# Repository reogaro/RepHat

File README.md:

# RepHat

"**R**epRap **E**xtension for **P**i"-**Hat**

Designed in Kicad. Open Source Hardware.

> [!CAUTION]
> This project is still in development and not ready for use!

A Raspberry Pi Hat for controlling stepper motors. Intended to be a [RAMPS](https://reprap.org/wiki/RAMPS_1.4) for the Raspberry Pi.

Built for use with LinuxCNC. See [here](https://github.com/reogaro/linuxcnc-pi4b-gpio) for some configuration examples.

## Features:

- 12-24 V Input Voltage
- 5V for Raspberry Pi with TI LMR51450 Switching Regulator
- Four Toshiba TB67S109AFTG Stepper Drivers
- Four endstop inputs with selectable voltages
- Input protection

## Current progress

[Schematic](output/schematic.pdf): Complete
[Routing](output/routing.pdf): Work in progress

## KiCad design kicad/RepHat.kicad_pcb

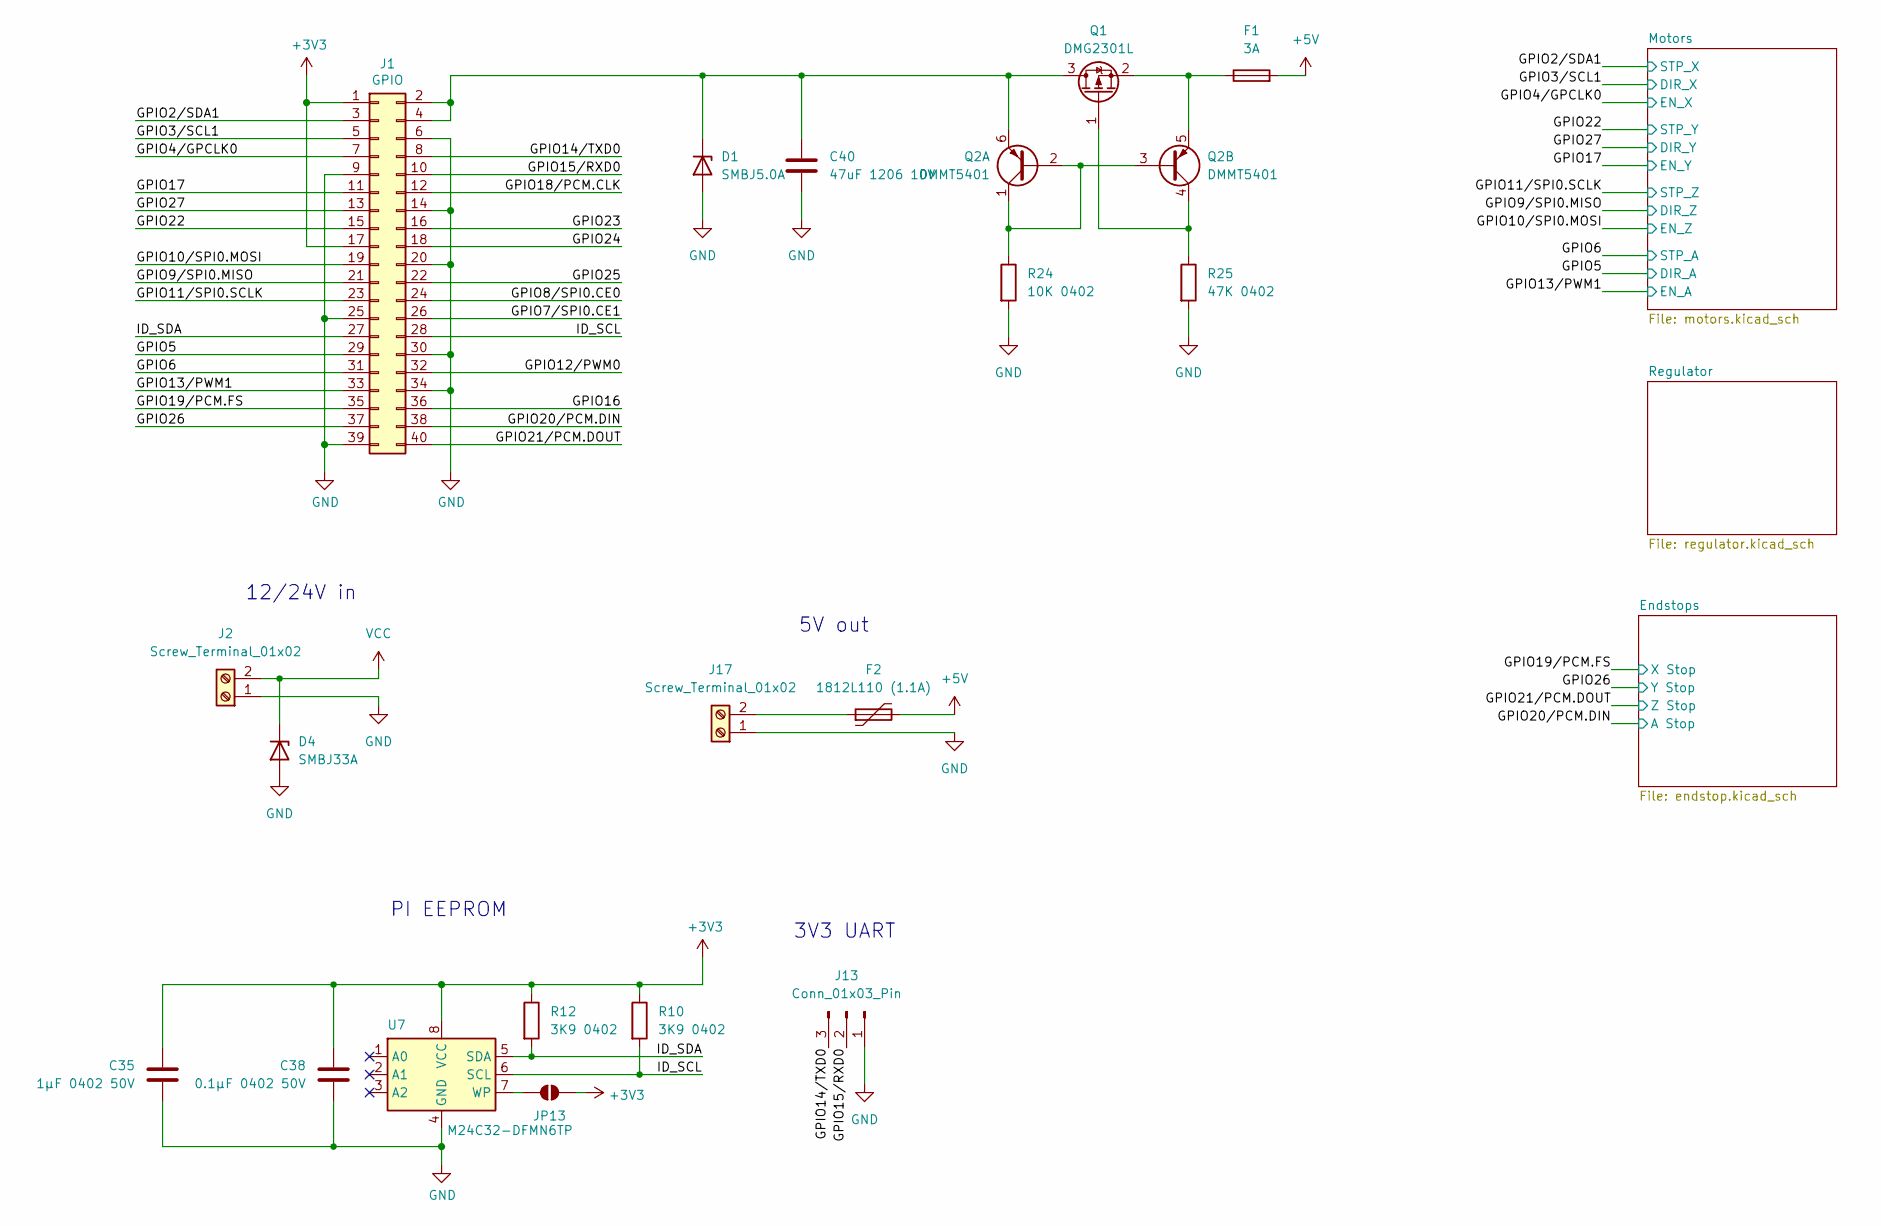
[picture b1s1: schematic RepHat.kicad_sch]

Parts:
C35: 1μF 0402 50V; C_0402_1005Metric
C38: 0.1μF 0402 50V; C_0402_1005Metric
C40: 47uF 1206 10V; C_1206_3216Metric
D1: SMBJ5.0A; D_SMB
D4: SMBJ33A; D_SMB
F1: 3A; Fuseholder_Littelfuse_Nano2_154x
F2: 1812L110 (1.1A); Fuse_1812_4532Metric
J1: GPIO; PinSocket_2x20_P2.54mm_Vertical
J2, J17: Screw_Terminal_01x02; TerminalBlock_bornier-2_P5.08mm
J13: Conn_01x03_Pin; PinHeader_1x03_P2.54mm_Vertical
JP13: ID_WP; SolderJumper-2_P1.3mm_Open_RoundedPad1.0x1.5mm
Q1: DMG2301L; SOT-23
Q2: DMMT5401; SOT-23-6
R10, R12: 3K9 0402; R_0402_1005Metric
R24: 10K 0402; R_0402_1005Metric
R25: 47K 0402; R_0402_1005Metric
U7: M24C32-DFMN6TP; SOIC-8_5.275x5.275mm_P1.27mm

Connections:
+3V3: C35.1, C38.1, J1.1, J1.17, JP13.2 (B), R10.1, R12.1, U7.8 (VCC); also elsewhere on the board
+5V: F1.2, F2.2; also elsewhere on the board
/GPIO2/SDA1: J1.3; also elsewhere on the board
/GPIO3/SCL1: J1.5; also elsewhere on the board
/GPIO4/GPCLK0: J1.7; also elsewhere on the board
/GPIO5: J1.29; also elsewhere on the board
/GPIO6: J1.31; also elsewhere on the board
/GPIO7/SPI0.CE1: J1.26
/GPIO8/SPI0.CE0: J1.24
/GPIO9/SPI0.MISO: J1.21; also elsewhere on the board
/GPIO10/SPI0.MOSI: J1.19; also elsewhere on the board
/GPIO11/SPI0.SCLK: J1.23; also elsewhere on the board
/GPIO12/PWM0: J1.32
/GPIO13/PWM1: J1.33; also elsewhere on the board
/GPIO14/TXD0: J1.8, J13.3
/GPIO15/RXD0: J1.10, J13.2
/GPIO16: J1.36
/GPIO17: J1.11; also elsewhere on the board
/GPIO18/PCM.CLK: J1.12
/GPIO19/PCM.FS: J1.35; also elsewhere on the board
/GPIO20/PCM.DIN: J1.38; also elsewhere on the board
/GPIO21/PCM.DOUT: J1.40; also elsewhere on the board
/GPIO22: J1.15; also elsewhere on the board
/GPIO23: J1.16
/GPIO24: J1.18
/GPIO25: J1.22
/GPIO26: J1.37; also elsewhere on the board
/GPIO27: J1.13; also elsewhere on the board
/ID_SCL: J1.28, R10.2, U7.6 (SCL)
/ID_SDA: J1.27, R12.2, U7.5 (SDA)
GND: C35.2, C38.2, C40.2, D1.2 (A), D4.2 (A), J1.6, J1.9, J1.14, J1.20, J1.25, J1.30, J1.34, J1.39, J2.1, J13.1, J17.1, R24.2, R25.2, U7.4 (GND); also elsewhere on the board
unnamed: C40.1, D1.1 (K), J1.2, J1.4, Q1.3 (D), Q2.6 (E1)
unnamed: F2.1, J17.2
unnamed: JP13.1 (A), U7.7 (WP)
unnamed: Q1.1 (G), Q2.4 (C2), R25.1
unnamed: F1.1, Q1.2 (S), Q2.5 (E2)
unnamed: Q2.1 (C1), Q2.2 (B1), Q2.3 (B2), R24.1
VCC: D4.1 (K), J2.2; also elsewhere on the board

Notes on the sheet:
12/24V in
PI EEPROM
5V out
3V3 UART

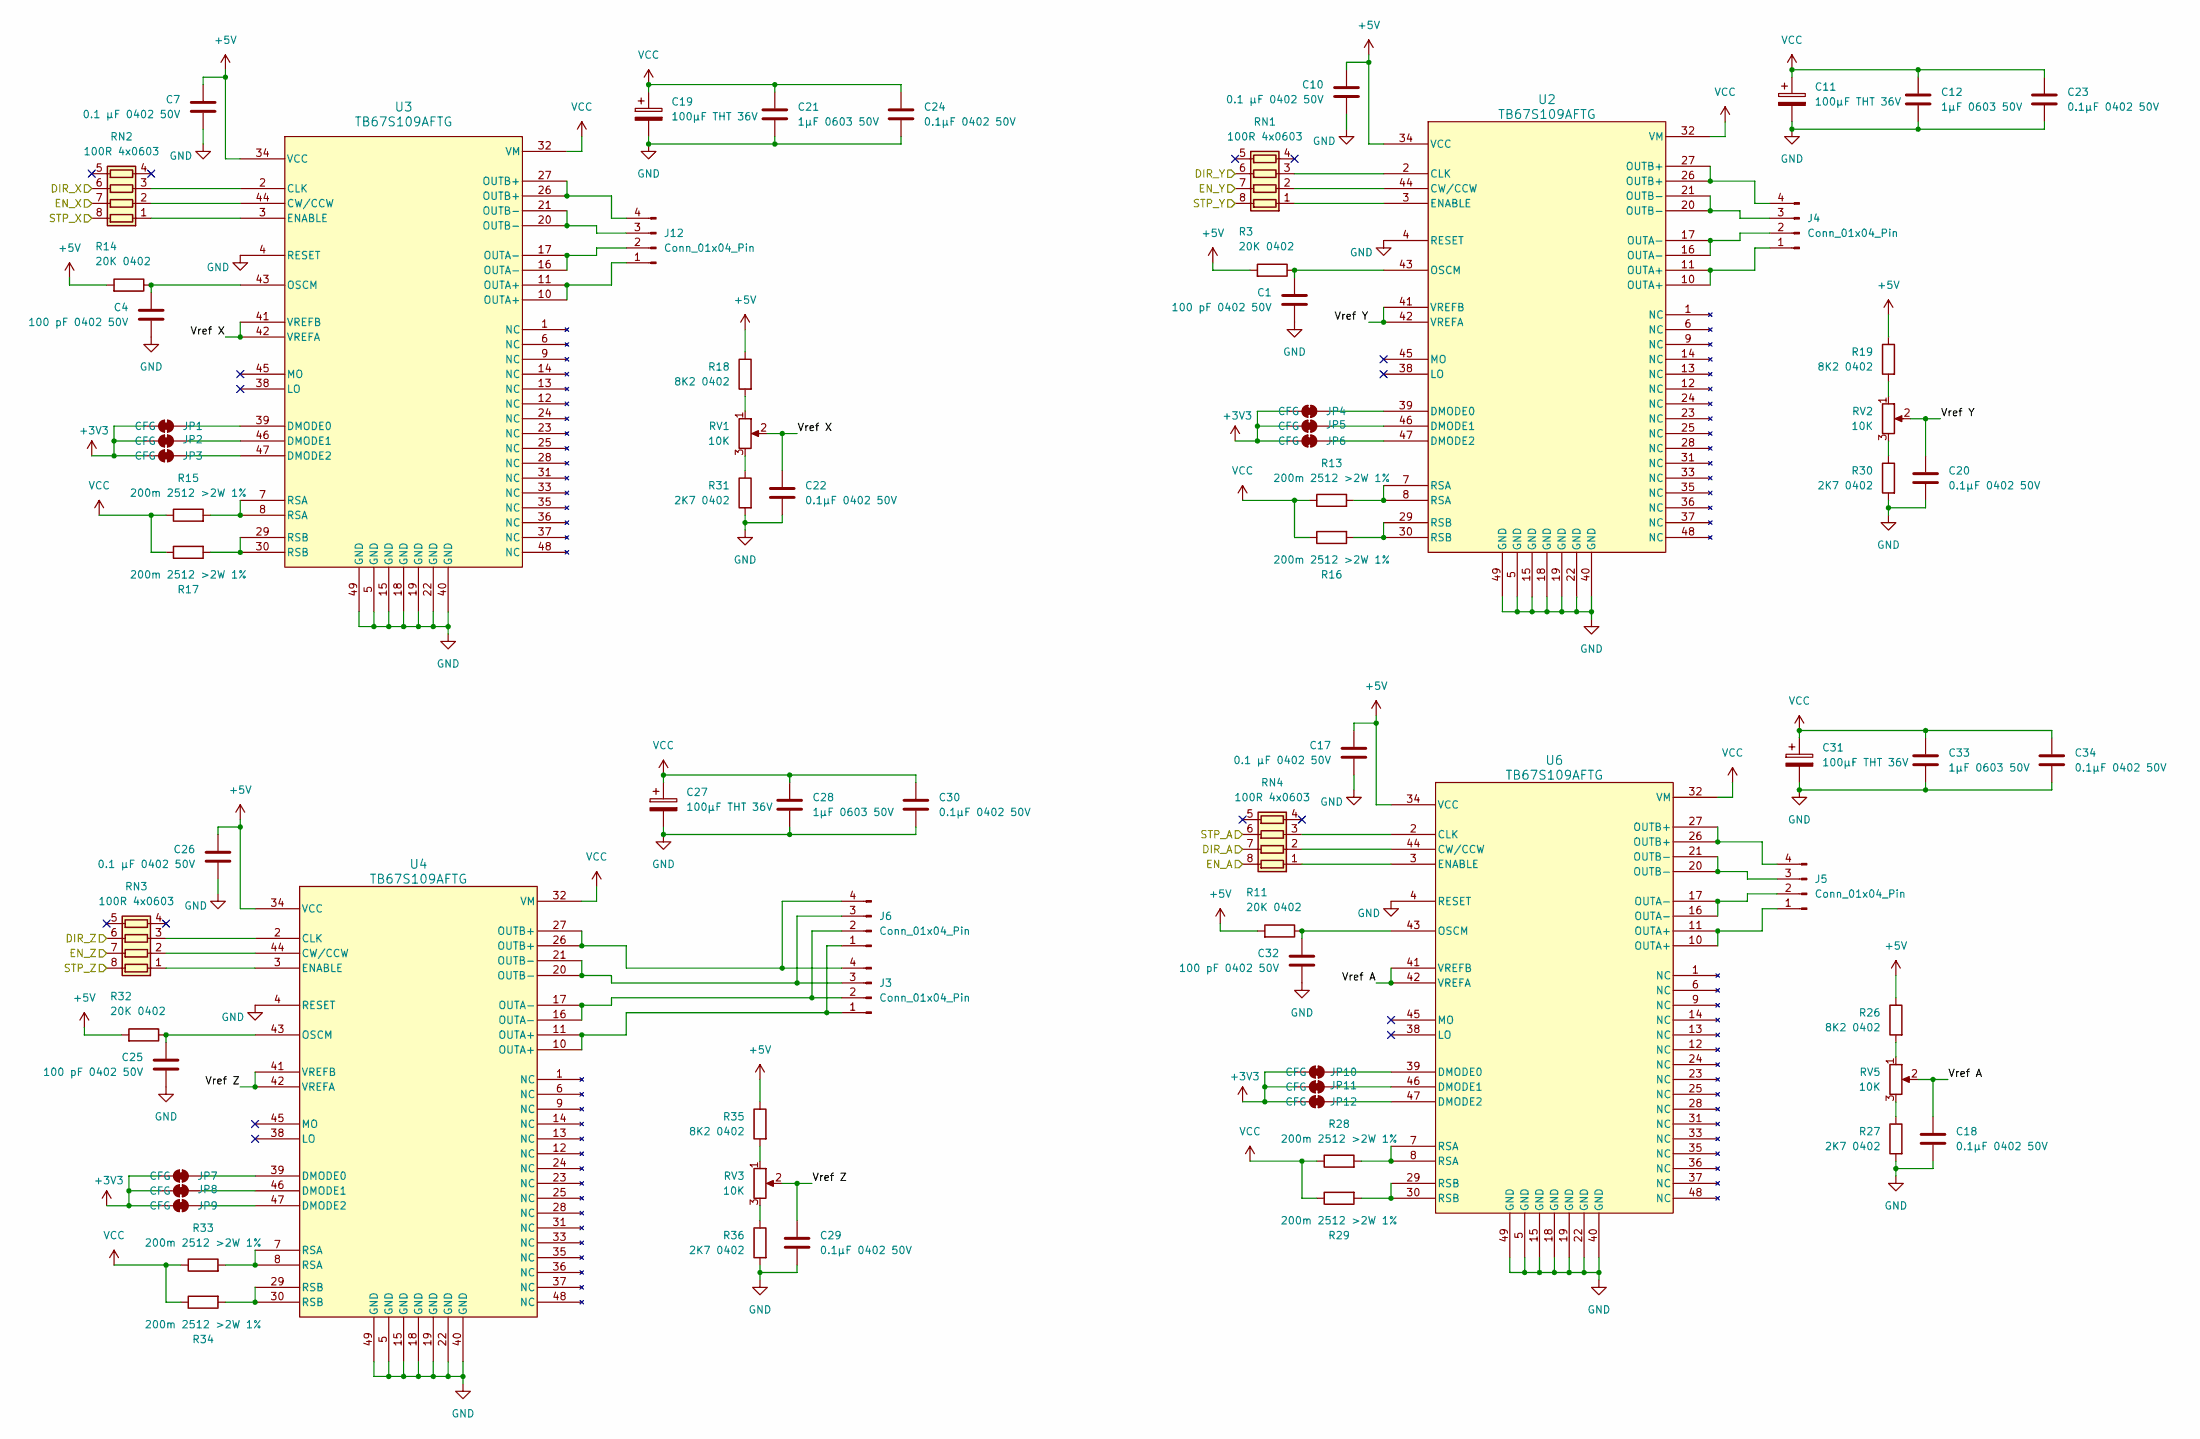
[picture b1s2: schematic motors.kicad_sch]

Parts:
C1, C4, C25, C32: 100 pF 0402 50V; C_0402_1005Metric
C7, C10, C17, C26: 0.1 μF 0402 50V; C_0402_1005Metric
C11, C19, C27, C31: 100μF THT 36V; C_Radial_D6.3mm_H11.0mm_P2.50mm
C12, C21, C28, C33: 1μF 0603 50V; C_0402_1005Metric
C18, C20, C22, C23, C24, C29, C30, C34: 0.1μF 0402 50V; C_0402_1005Metric
J3, J4, J5, J6, J12: Conn_01x04_Pin; S4B-XH-SM4-TB
JP1, JP2, JP3, JP4, JP5, JP6, JP7, JP8, JP9, JP10, JP11, JP12: CFG; SolderJumper-2_P1.3mm_Bridged_RoundedPad1.0x1.5mm
R3, R11, R14, R32: 20K 0402; R_0402_1005Metric
R13, R15, R16, R17, R28, R29, R33, R34: 200m 2512 >2W 1%; R_2512_6332Metric
R18, R19, R26, R35: 8K2 0402; R_0402_1005Metric
R27, R30, R31, R36: 2K7 0402; R_0402_1005Metric
RN1, RN2, RN3, RN4: 100R 4x0603; R_Array_Concave_4x0603
RV1, RV2, RV3, RV5: 10K; Potentiometer_Bourns_TC33X_Vertical
U2, U3, U4, U6: TB67S109AFTG; QFN-48-1EP_7x7mm_P0.5mm_EP5.45x5.45mm_ThermalVias

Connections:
+3V3: JP1.1 (A), JP2.1 (A), JP3.1 (A), JP4.1 (A), JP5.1 (A), JP6.1 (A), JP7.1 (A), JP8.1 (A), JP9.1 (A), JP10.1 (A), JP11.1 (A), JP12.1 (A); also elsewhere on the board
+5V: C7.1, C10.1, C17.1, C26.1, R3.2, R11.2, R14.2, R18.1, R19.1, R26.1, R32.2, R35.1, U2.34 (VCC), U3.34 (VCC), U4.34 (VCC), U6.34 (VCC); also elsewhere on the board
/GPIO2/SDA1: RN2.8 (R1.2); also elsewhere on the board
/GPIO3/SCL1: RN2.6 (R3.2); also elsewhere on the board
/GPIO4/GPCLK0: RN2.7 (R2.2); also elsewhere on the board
/GPIO5: RN4.7 (R2.2); also elsewhere on the board
/GPIO6: RN4.6 (R3.2); also elsewhere on the board
/GPIO9/SPI0.MISO: RN3.6 (R3.2); also elsewhere on the board
/GPIO10/SPI0.MOSI: RN3.7 (R2.2); also elsewhere on the board
/GPIO11/SPI0.SCLK: RN3.8 (R1.2); also elsewhere on the board
/GPIO13/PWM1: RN4.8 (R1.2); also elsewhere on the board
/GPIO17: RN1.7 (R2.2); also elsewhere on the board
/GPIO22: RN1.8 (R1.2); also elsewhere on the board
/GPIO27: RN1.6 (R3.2); also elsewhere on the board
/Motors/Vref A: C18.1, RV5.2, U6.41 (VREFB), U6.42 (VREFA)
/Motors/Vref X: C22.1, RV1.2, U3.41 (VREFB), U3.42 (VREFA)
/Motors/Vref Y: C20.1, RV2.2, U2.41 (VREFB), U2.42 (VREFA)
/Motors/Vref Z: C29.1, RV3.2, U4.41 (VREFB), U4.42 (VREFA)
GND: C1.2, C4.2, C7.2, C10.2, C11.2, C12.2, C17.2, C18.2, C19.2, C20.2, C21.2, C22.2, C23.2, C24.2, C25.2, C26.2, C27.2, C28.2, C29.2, C30.2, C31.2, C32.2, C33.2, C34.2, R27.2, R30.2, R31.2, R36.2, U2.4 (RESET), U2.5 (GND), U2.15 (GND), U2.18 (GND), U2.19 (GND), U2.22 (GND), U2.40 (GND), U2.49 (GND), U3.4 (RESET), U3.5 (GND), U3.15 (GND), U3.18 (GND), U3.19 (GND), U3.22 (GND), U3.40 (GND), U3.49 (GND), U4.4 (RESET), U4.5 (GND), U4.15 (GND), U4.18 (GND), U4.19 (GND), U4.22 (GND), U4.40 (GND), U4.49 (GND), U6.4 (RESET), U6.5 (GND), U6.15 (GND), U6.18 (GND), U6.19 (GND), U6.22 (GND), U6.40 (GND), U6.49 (GND); also elsewhere on the board
unnamed: J3.1, J6.1, U4.10 (OUTA+), U4.11 (OUTA+)
unnamed: J3.2, J6.2, U4.16 (OUTA-), U4.17 (OUTA-)
unnamed: J3.3, J6.3, U4.20 (OUTB-), U4.21 (OUTB-)
unnamed: J3.4, J6.4, U4.26 (OUTB+), U4.27 (OUTB+)
unnamed: J4.1, U2.10 (OUTA+), U2.11 (OUTA+)
unnamed: J4.2, U2.16 (OUTA-), U2.17 (OUTA-)
unnamed: J4.3, U2.20 (OUTB-), U2.21 (OUTB-)
unnamed: J4.4, U2.26 (OUTB+), U2.27 (OUTB+)
unnamed: J5.1, U6.10 (OUTA+), U6.11 (OUTA+)
unnamed: J5.2, U6.16 (OUTA-), U6.17 (OUTA-)
unnamed: J5.3, U6.20 (OUTB-), U6.21 (OUTB-)
unnamed: J5.4, U6.26 (OUTB+), U6.27 (OUTB+)
unnamed: J12.1, U3.10 (OUTA+), U3.11 (OUTA+)
unnamed: J12.2, U3.16 (OUTA-), U3.17 (OUTA-)
unnamed: J12.3, U3.20 (OUTB-), U3.21 (OUTB-)
unnamed: J12.4, U3.26 (OUTB+), U3.27 (OUTB+)
unnamed: JP1.2 (B), U3.39 (DMODE0)
unnamed: JP2.2 (B), U3.46 (DMODE1)
unnamed: JP3.2 (B), U3.47 (DMODE2)
unnamed: JP4.2 (B), U2.39 (DMODE0)
unnamed: JP5.2 (B), U2.46 (DMODE1)
unnamed: JP6.2 (B), U2.47 (DMODE2)
unnamed: JP7.2 (B), U4.39 (DMODE0)
unnamed: JP8.2 (B), U4.46 (DMODE1)
unnamed: JP9.2 (B), U4.47 (DMODE2)
unnamed: JP10.2 (B), U6.39 (DMODE0)
unnamed: JP11.2 (B), U6.46 (DMODE1)
unnamed: JP12.2 (B), U6.47 (DMODE2)
unnamed: R13.2, U2.7 (RSA), U2.8 (RSA)
unnamed: R15.2, U3.7 (RSA), U3.8 (RSA)
unnamed: R16.2, U2.29 (RSB), U2.30 (RSB)
unnamed: R17.2, U3.29 (RSB), U3.30 (RSB)
unnamed: R18.2, RV1.1
unnamed: R19.2, RV2.1
unnamed: R26.2, RV5.1
unnamed: R27.1, RV5.3
unnamed: R28.2, U6.7 (RSA), U6.8 (RSA)
unnamed: R29.2, U6.29 (RSB), U6.30 (RSB)
unnamed: R30.1, RV2.3
unnamed: R31.1, RV1.3
unnamed: R33.2, U4.7 (RSA), U4.8 (RSA)
unnamed: R34.2, U4.29 (RSB), U4.30 (RSB)
unnamed: R35.2, RV3.1
unnamed: R36.1, RV3.3
unnamed: RN1.1 (R1.1), U2.3 (ENABLE)
unnamed: RN1.2 (R2.1), U2.44 (CW/CCW)
unnamed: RN1.3 (R3.1), U2.2 (CLK)
unnamed: RN2.1 (R1.1), U3.3 (ENABLE)
unnamed: RN2.2 (R2.1), U3.44 (CW/CCW)
unnamed: RN2.3 (R3.1), U3.2 (CLK)
unnamed: RN3.1 (R1.1), U4.3 (ENABLE)
unnamed: RN3.2 (R2.1), U4.44 (CW/CCW)
unnamed: RN3.3 (R3.1), U4.2 (CLK)
unnamed: RN4.1 (R1.1), U6.3 (ENABLE)
unnamed: RN4.2 (R2.1), U6.44 (CW/CCW)
unnamed: RN4.3 (R3.1), U6.2 (CLK)
unnamed: C1.1, R3.1, U2.43 (OSCM)
unnamed: C4.1, R14.1, U3.43 (OSCM)
unnamed: C25.1, R32.1, U4.43 (OSCM)
unnamed: C32.1, R11.1, U6.43 (OSCM)
VCC: C11.1, C12.1, C19.1, C21.1, C23.1, C24.1, C27.1, C28.1, C30.1, C31.1, C33.1, C34.1, R13.1, R15.1, R16.1, R17.1, R28.1, R29.1, R33.1, R34.1, U2.32 (VM), U3.32 (VM), U4.32 (VM), U6.32 (VM); also elsewhere on the board

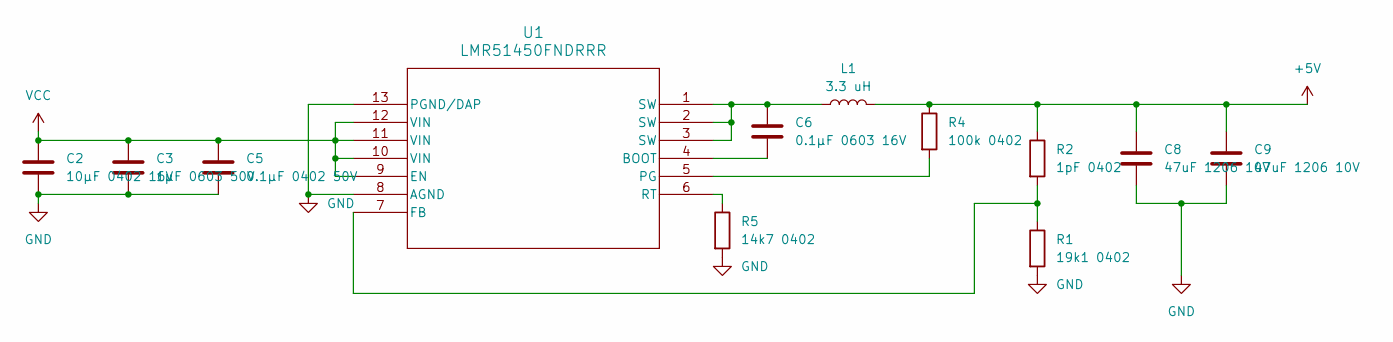
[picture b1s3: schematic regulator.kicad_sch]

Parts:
C2: 10μF 0402 16V; C_0402_1005Metric
C3: 1μF 0603 50V; C_0402_1005Metric
C5: 0.1μF 0402 50V; C_0402_1005Metric
C6: 0.1μF 0603 16V; C_0402_1005Metric
C8, C9: 47uF 1206 10V; C_1206_3216Metric
L1: 3.3 uH; L_Wuerth_WE-PD4-Typ-L
R1: 19k1 0402; R_0402_1005Metric
R2: 1pF 0402; R_0402_1005Metric
R4: 100k 0402; R_0402_1005Metric
R5: 14k7 0402; R_0402_1005Metric
U1: LMR51450FNDRRR; WSON_SDRRR_TEX

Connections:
+5V: C8.1, C9.1, L1.1, R2.1, R4.1; also elsewhere on the board
GND: C2.2, C3.2, C5.2, C8.2, C9.2, R1.2, R5.2, U1.8 (AGND), U1.13 (PGND/DAP); also elsewhere on the board
unnamed: C6.1, L1.2, U1.1 (SW), U1.2 (SW), U1.3 (SW)
unnamed: C6.2, U1.4 (BOOT)
unnamed: R1.1, R2.2, U1.7 (FB)
unnamed: R4.2, U1.5 (PG)
unnamed: R5.1, U1.6 (RT)
VCC: C2.1, C3.1, C5.1, U1.9 (EN), U1.10 (VIN), U1.11 (VIN), U1.12 (VIN); also elsewhere on the board

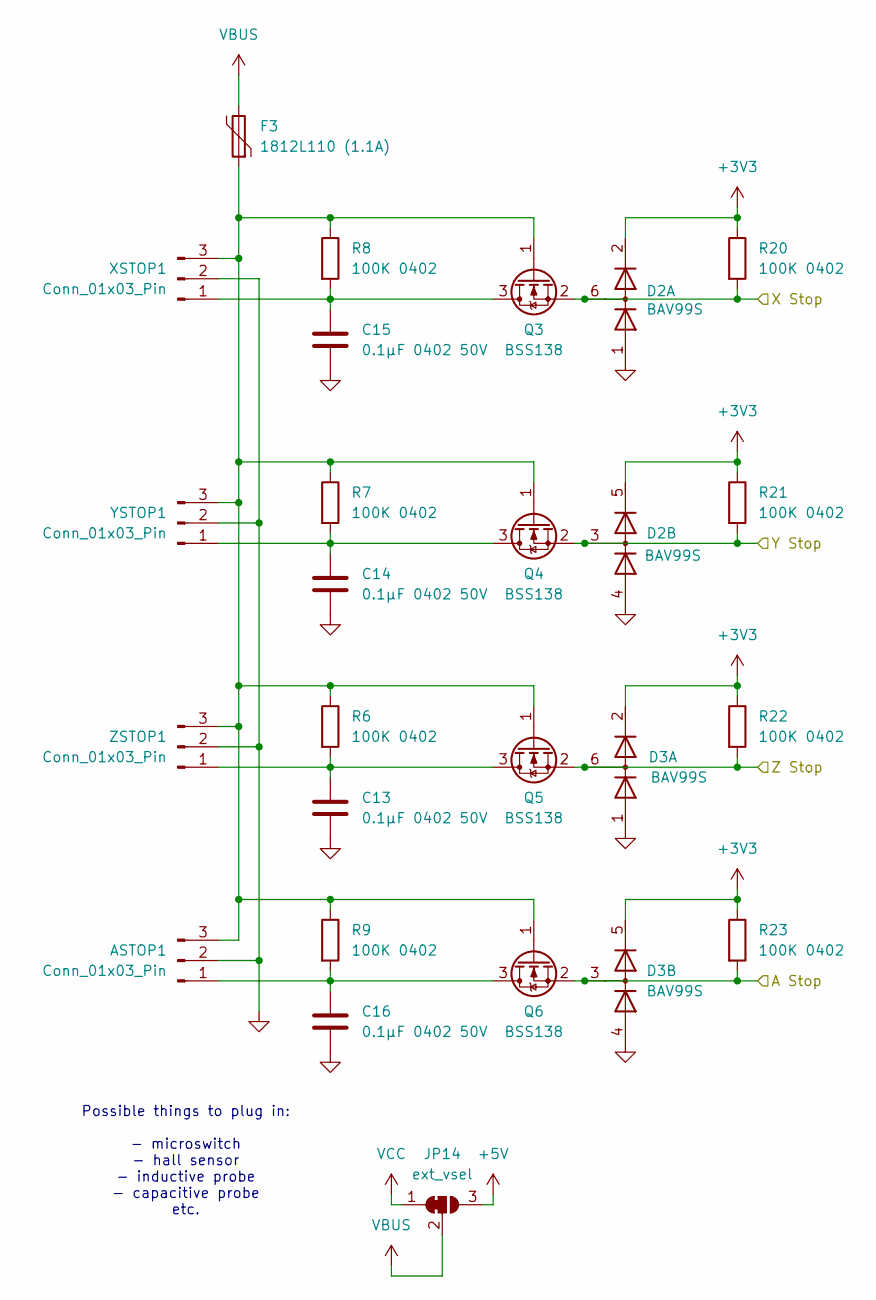
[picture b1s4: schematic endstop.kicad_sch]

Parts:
ASTOP1: Conn_01x03_Pin; S3B-XH-SM4-TB
C13, C14, C15, C16: 0.1μF 0402 50V; C_0402_1005Metric
D2, D3: BAV99S; SOT-363_SC-70-6
F3: 1812L110 (1.1A); Fuse_1812_4532Metric
JP14: ext_vsel; SolderJumper-3_P1.3mm_Bridged12_RoundedPad1.0x1.5mm
Q3, Q4, Q5, Q6: BSS138; SOT-23
R6, R7, R8, R9, R20, R21, R22, R23: 100K 0402; R_0402_1005Metric
XSTOP1: Conn_01x03_Pin; S3B-XH-SM4-TB
YSTOP1: Conn_01x03_Pin; S3B-XH-SM4-TB
ZSTOP1: Conn_01x03_Pin; S3B-XH-SM4-TB

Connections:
+3V3: D2.2 (K2), D2.5 (K4), D3.2 (K2), D3.5 (K4), R20.1, R21.1, R22.1, R23.1; also elsewhere on the board
+5V: JP14.3 (B); also elsewhere on the board
/GPIO19/PCM.FS: D2.6 (K3A4), Q3.2 (S), R20.2; also elsewhere on the board
/GPIO20/PCM.DIN: D3.3 (K1A2), Q6.2 (S), R23.2; also elsewhere on the board
/GPIO21/PCM.DOUT: D3.6 (K3A4), Q5.2 (S), R22.2; also elsewhere on the board
/GPIO26: D2.3 (K1A2), Q4.2 (S), R21.2; also elsewhere on the board
GND: ASTOP1.2, C13.2, C14.2, C15.2, C16.2, D2.1 (A1), D2.4 (A3), D3.1 (A1), D3.4 (A3), XSTOP1.2, YSTOP1.2, ZSTOP1.2; also elsewhere on the board
unnamed: ASTOP1.1, C16.1, Q6.3 (D), R9.2
unnamed: ASTOP1.3, F3.1, Q3.1 (G), Q4.1 (G), Q5.1 (G), Q6.1 (G), R6.1, R7.1, R8.1, R9.1, XSTOP1.3, YSTOP1.3, ZSTOP1.3
unnamed: C15.1, Q3.3 (D), R8.2, XSTOP1.1
unnamed: C14.1, Q4.3 (D), R7.2, YSTOP1.1
unnamed: C13.1, Q5.3 (D), R6.2, ZSTOP1.1
VBUS: F3.2, JP14.2 (C)
VCC: JP14.1 (A); also elsewhere on the board

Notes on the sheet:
Possible things to plug in: - microswitch - hall sensor - inductive probe - capacitive probe etc.

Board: 2 copper layers, 132 parts (1 on the bottom side), 105 nets, no tracks yet.

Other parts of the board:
MH1, MH2, MH3, MH4: MountingHole_2.7mm_M2.5

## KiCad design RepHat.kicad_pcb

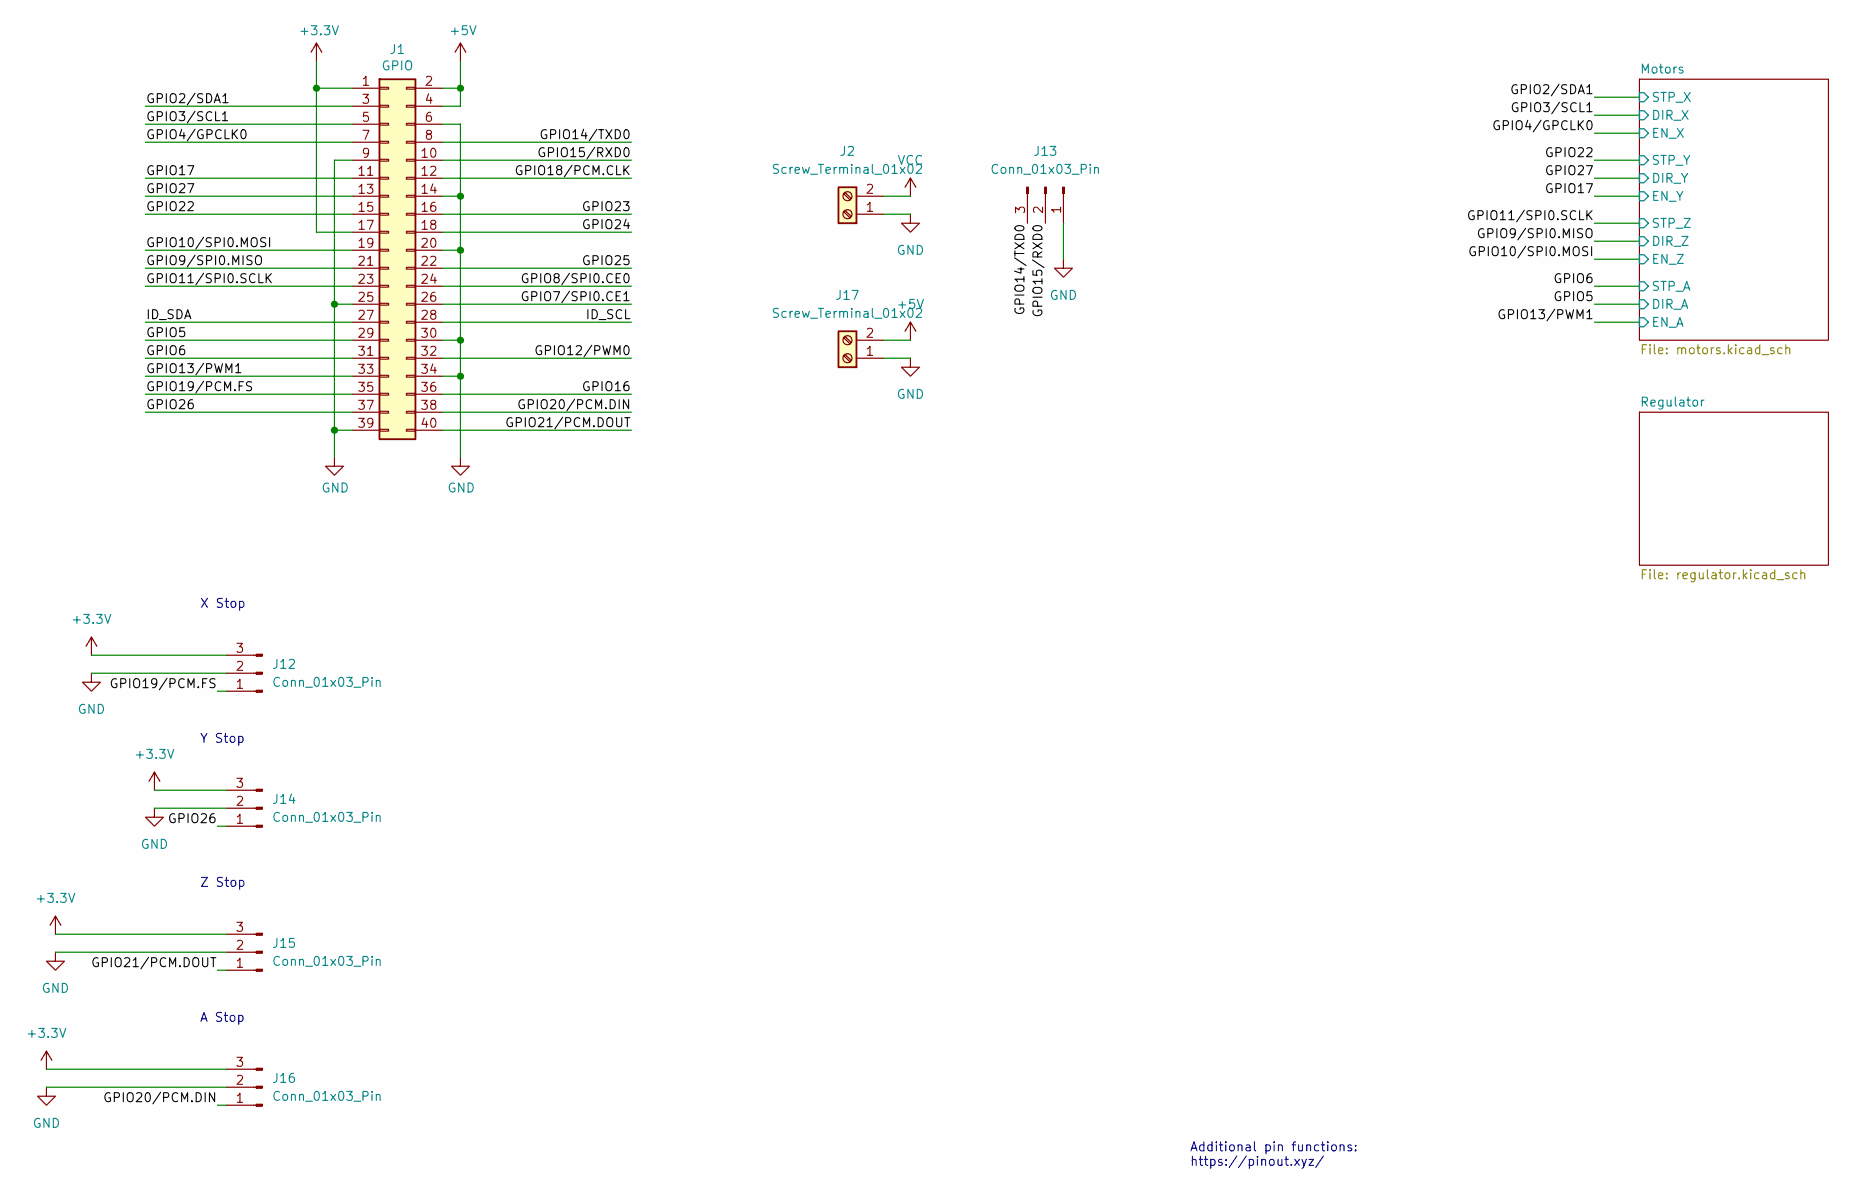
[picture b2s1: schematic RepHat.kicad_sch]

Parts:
J1: GPIO; PinSocket_2x20_P2.54mm_Vertical
J2, J17: Screw_Terminal_01x02; TerminalBlock_WAGO_236-102_1x02_P5.00mm_45Degree
J12, J13, J14, J15, J16: Conn_01x03_Pin; JST_XH_B3B-XH-A_1x03_P2.50mm_Vertical

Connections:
+5V: J1.2, J1.4, J17.2; also elsewhere on the board
/GPIO2/SDA1: J1.3; also elsewhere on the board
/GPIO3/SCL1: J1.5; also elsewhere on the board
/GPIO4/GPCLK0: J1.7; also elsewhere on the board
/GPIO5: J1.29; also elsewhere on the board
/GPIO6: J1.31; also elsewhere on the board
/GPIO7/SPI0.CE1: J1.26
/GPIO8/SPI0.CE0: J1.24
/GPIO9/SPI0.MISO: J1.21; also elsewhere on the board
/GPIO10/SPI0.MOSI: J1.19; also elsewhere on the board
/GPIO11/SPI0.SCLK: J1.23; also elsewhere on the board
/GPIO12/PWM0: J1.32
/GPIO13/PWM1: J1.33; also elsewhere on the board
/GPIO14/TXD0: J1.8, J13.3
/GPIO15/RXD0: J1.10, J13.2
/GPIO16: J1.36
/GPIO17: J1.11; also elsewhere on the board
/GPIO18/PCM.CLK: J1.12
/GPIO19/PCM.FS: J1.35, J12.1
/GPIO20/PCM.DIN: J1.38, J16.1
/GPIO21/PCM.DOUT: J1.40, J15.1
/GPIO22: J1.15; also elsewhere on the board
/GPIO23: J1.16
/GPIO24: J1.18
/GPIO25: J1.22
/GPIO26: J1.37, J14.1
/GPIO27: J1.13; also elsewhere on the board
/ID_SCL: J1.28
/ID_SDA: J1.27
GND: J1.6, J1.9, J1.14, J1.20, J1.25, J1.30, J1.34, J1.39, J2.1, J12.2, J13.1, J14.2, J15.2, J16.2, J17.1; also elsewhere on the board
VCC: J2.2; also elsewhere on the board

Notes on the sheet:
X Stop
Additional pin functions: https://pinout.xyz/
Z Stop
Y Stop
A Stop

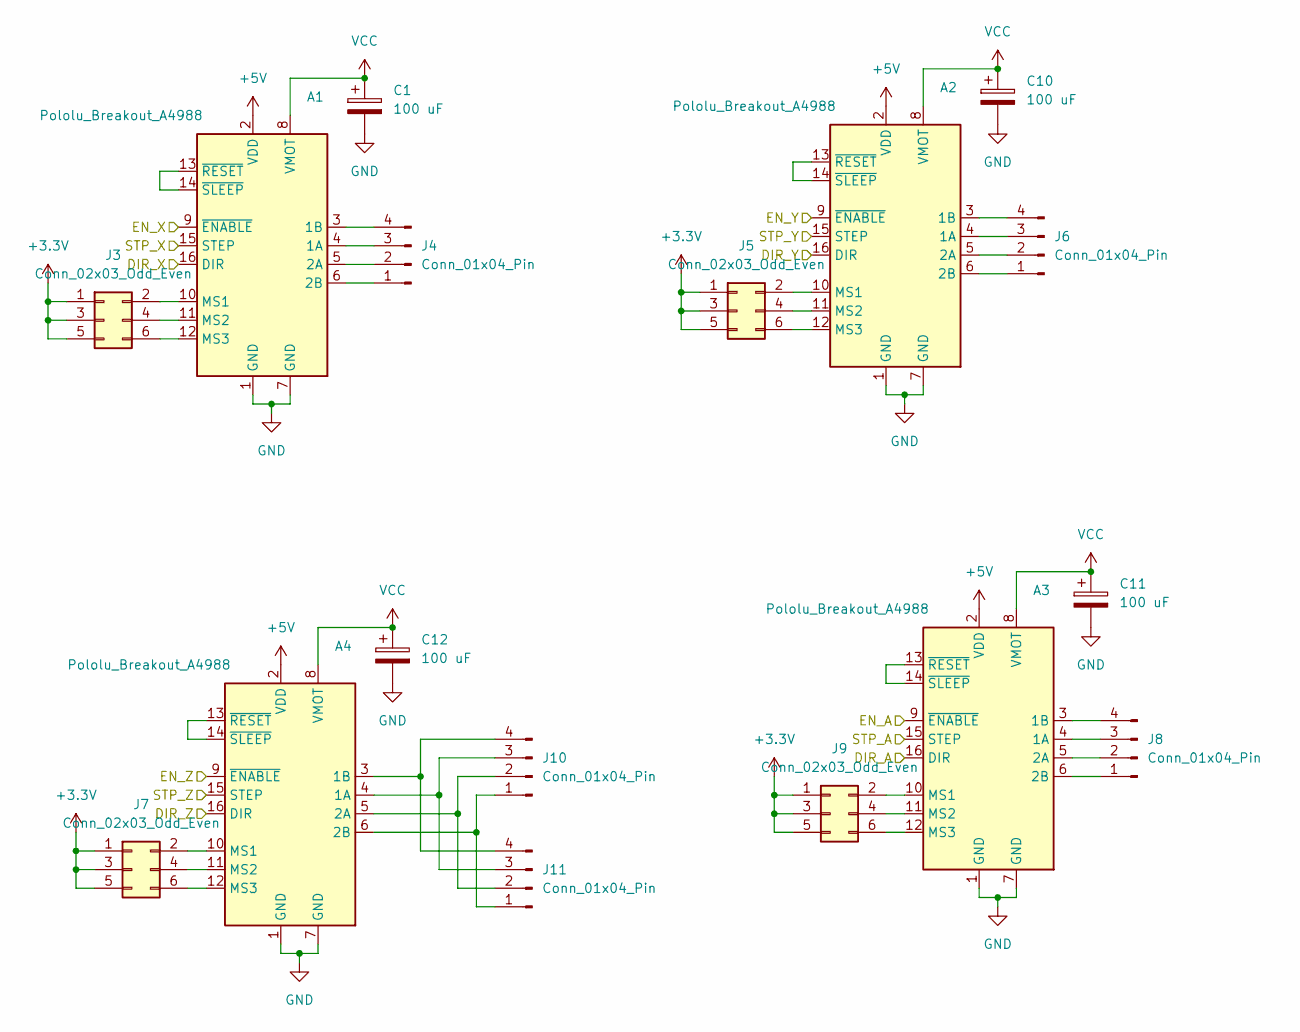
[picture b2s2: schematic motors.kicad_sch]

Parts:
A1, A2, A3, A4: Pololu_Breakout_A4988; Pololu_Breakout-16_15.2x20.3mm
C1, C10, C11, C12: 100 uF; C_Disc_D3.0mm_W1.6mm_P2.50mm
J3, J5, J7, J9: Conn_02x03_Odd_Even; PinHeader_2x03_P2.54mm_Vertical
J4, J6, J8, J10, J11: Conn_01x04_Pin; JST_XH_B4B-XH-A_1x04_P2.50mm_Vertical

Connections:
+5V: A1.2 (VDD), A2.2 (VDD), A3.2 (VDD), A4.2 (VDD); also elsewhere on the board
/GPIO2/SDA1: A1.15 (STEP); also elsewhere on the board
/GPIO3/SCL1: A1.16 (DIR); also elsewhere on the board
/GPIO4/GPCLK0: A1.9 (~ENABLE); also elsewhere on the board
/GPIO5: A3.16 (DIR); also elsewhere on the board
/GPIO6: A3.15 (STEP); also elsewhere on the board
/GPIO9/SPI0.MISO: A4.16 (DIR); also elsewhere on the board
/GPIO10/SPI0.MOSI: A4.9 (~ENABLE); also elsewhere on the board
/GPIO11/SPI0.SCLK: A4.15 (STEP); also elsewhere on the board
/GPIO13/PWM1: A3.9 (~ENABLE); also elsewhere on the board
/GPIO17: A2.9 (~ENABLE); also elsewhere on the board
/GPIO22: A2.15 (STEP); also elsewhere on the board
/GPIO27: A2.16 (DIR); also elsewhere on the board
GND: A1.1 (GND), A1.7 (GND), A2.1 (GND), A2.7 (GND), A3.1 (GND), A3.7 (GND), A4.1 (GND), A4.7 (GND), C1.2, C10.2, C11.2, C12.2; also elsewhere on the board
unnamed: A1.4 (1A), J4.3
unnamed: A1.3 (1B), J4.4
unnamed: A1.5 (2A), J4.2
unnamed: A1.6 (2B), J4.1
unnamed: A1.10 (MS1), J3.2
unnamed: A1.11 (MS2), J3.4
unnamed: A1.12 (MS3), J3.6
unnamed: A1.13 (~RESET), A1.14 (~SLEEP)
unnamed: A2.4 (1A), J6.3
unnamed: A2.3 (1B), J6.4
unnamed: A2.5 (2A), J6.2
unnamed: A2.6 (2B), J6.1
unnamed: A2.10 (MS1), J5.2
unnamed: A2.11 (MS2), J5.4
unnamed: A2.12 (MS3), J5.6
unnamed: A2.13 (~RESET), A2.14 (~SLEEP)
unnamed: A3.4 (1A), J8.3
unnamed: A3.3 (1B), J8.4
unnamed: A3.5 (2A), J8.2
unnamed: A3.6 (2B), J8.1
unnamed: A3.10 (MS1), J9.2
unnamed: A3.11 (MS2), J9.4
unnamed: A3.12 (MS3), J9.6
unnamed: A3.13 (~RESET), A3.14 (~SLEEP)
unnamed: A4.4 (1A), J10.3, J11.3
unnamed: A4.3 (1B), J10.4, J11.4
unnamed: A4.5 (2A), J10.2, J11.2
unnamed: A4.6 (2B), J10.1, J11.1
unnamed: A4.10 (MS1), J7.2
unnamed: A4.11 (MS2), J7.4
unnamed: A4.12 (MS3), J7.6
unnamed: A4.13 (~RESET), A4.14 (~SLEEP)
VCC: A1.8 (VMOT), A2.8 (VMOT), A3.8 (VMOT), A4.8 (VMOT), C1.1, C10.1, C11.1, C12.1; also elsewhere on the board

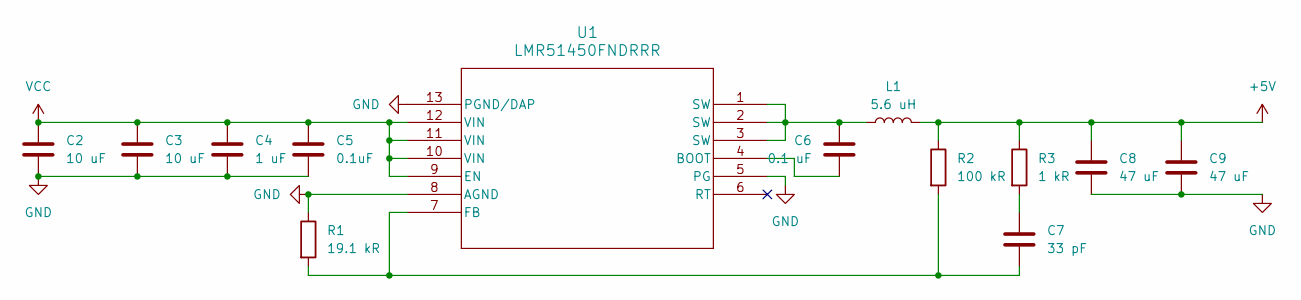
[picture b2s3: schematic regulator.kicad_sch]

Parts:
C2, C3: 10 uF; C_0603_1608Metric
C4: 1 uF; C_0603_1608Metric
C5: 0.1uF; C_0603_1608Metric
C6: 0.1 uF; C_0603_1608Metric
C7: 33 pF; C_0603_1608Metric
C8, C9: 47 uF; C_1206_3216Metric
L1: 5.6 uH; L_Wuerth_WE-PD4-Typ-L
R1: 19.1 kR; R_0603_1608Metric
R2: 100 kR; R_0603_1608Metric
R3: 1 kR; R_0603_1608Metric
U1: LMR51450FNDRRR; WSON_SDRRR_TEX

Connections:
+5V: C8.1, C9.1, L1.1, R2.1, R3.1; also elsewhere on the board
GND: C2.2, C3.2, C4.2, C5.2, C8.2, C9.2, R1.1, U1.5 (PG), U1.8 (AGND), U1.13 (PGND/DAP); also elsewhere on the board
unnamed: C6.1, L1.2, U1.1 (SW), U1.2 (SW), U1.3 (SW)
unnamed: C7.1, R3.2
unnamed: C6.2, U1.4 (BOOT)
unnamed: C7.2, R1.2, R2.2, U1.7 (FB)
VCC: C2.1, C3.1, C4.1, C5.1, U1.9 (EN), U1.10 (VIN), U1.11 (VIN), U1.12 (VIN); also elsewhere on the board

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
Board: 2 copper layers, 42 parts (1 on the bottom side), 59 nets, no tracks yet.

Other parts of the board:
MH1, MH2, MH3, MH4: MountingHole_2.7mm_M2.5

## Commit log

2024-06-01 initial fixes
2024-06-02 Endstops buffered & regulator 1MHz
2024-06-04 TMC2209 progress
2024-06-04 reorganized files
2024-06-05 Miniaturizing the stepper drivers. They're still too big
2024-06-11 TMC2209->TMC2100, endstop protection optimization
2024-06-12 DRV8825 schematic
2024-06-12 PCB redo
2024-06-21 schematic candidate 0
2024-06-28 Toshiba TB67S109A stepper driver
2024-07-02 new level shifter: bss138 transistors
2024-07-02 TB67S109A schematic wired
2024-07-02 cleanup
2024-07-02 add github actions
2024-09-10 schematic finished
2024-09-23 layout progress
2024-09-24 documentation refresh
